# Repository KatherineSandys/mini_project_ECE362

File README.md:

# ECE362_Mini_Project

# Submission 2:

## Internal Peripherals: ADC DAC GPIO SPI I2C

## External Peripherals: Analog SPI I2C

## What are you making?

### Splitting project description into describing the physical hardware, and then what it will be doing.

### Hardware Description:
ILI9341 driven 320x240 3.5" TFT Display controller via SPI.
I2C button matrix (Adafruit Product ID 1616, Trellis 4x4 Keypad) with internal LEDs. LEDs are controlled independently of whether buttons are pushed or not. Button state can be read via I2C, and LED state written via I2C.
Touchscreen on top of TFT: Resistive touchscreen overlay, read via 2 ADC channels giving XY coordinates of touch. calibrated via mapping recorded touch points to position user was told to press on the LCD screen (this is the standard way to calibrate these). Some GPIO used to control additional control signals such as D/C line.
(Tentative, will use if time allows for game menu, otherwise will use button matrix)
-Note- both display and keypad matrix are already owned by a team member and don't need to be purchased.
Audio output: Simple audio output via circuitry used in class to headphones. Will use DAC along with DMA to output music during gameplay.

### Operational Description:
A memory game using buttons. The screen will show you the buttons that need to be pressed along with the corresponding buttons lighting up. 
The screen will show what order each needs to be pressed in by superimposing a number on the representation of the buttons on the screen. 
The screen will only show these details for a short period of time, during which the player must memorize this sequence to be able to win. 
Once the screen stops showing the order and the buttons, the user must then press the buttons in the correct order. 
They have an unlimited amount of time to do so. The more buttons pressed and more sequences that they have been through, the higher the score will be.
Once the display has stopped showing what buttons should be pressed, it will display points, a count-up timer, and a representation of what buttons are currently neing pressed.
Of course, Tetris music will be played during operation for the nice ambiance it has.

## How will you demonstrate it?
The game will be played with music in the background.
The aim is to score as many points possible as you complete the game.
As you press the buttons in the correct order for a given problem the score will increase.
If you do not press the correct buttons in the correct order you do not achieve any remaining points for that level.

## What are the criteria for a successful project?

### Hardware requirements:
full control over contents of display
touchscreen properly calibrated, touch points properly map to intended location of press on the LCD.
no visible delay between pressing of keypad and any requisite lighting of keys.
audible audio, with no unpleasant crackles or pops caused by software delay.

### Software
Points are only awarded for correct gameplay, i.e. only when buttons are pressed in the sequence directed.
Display properly shows the buttons to be pressed as well as the sequence in which they should be pressed.
LEDs on keyad light when sequence is shown.

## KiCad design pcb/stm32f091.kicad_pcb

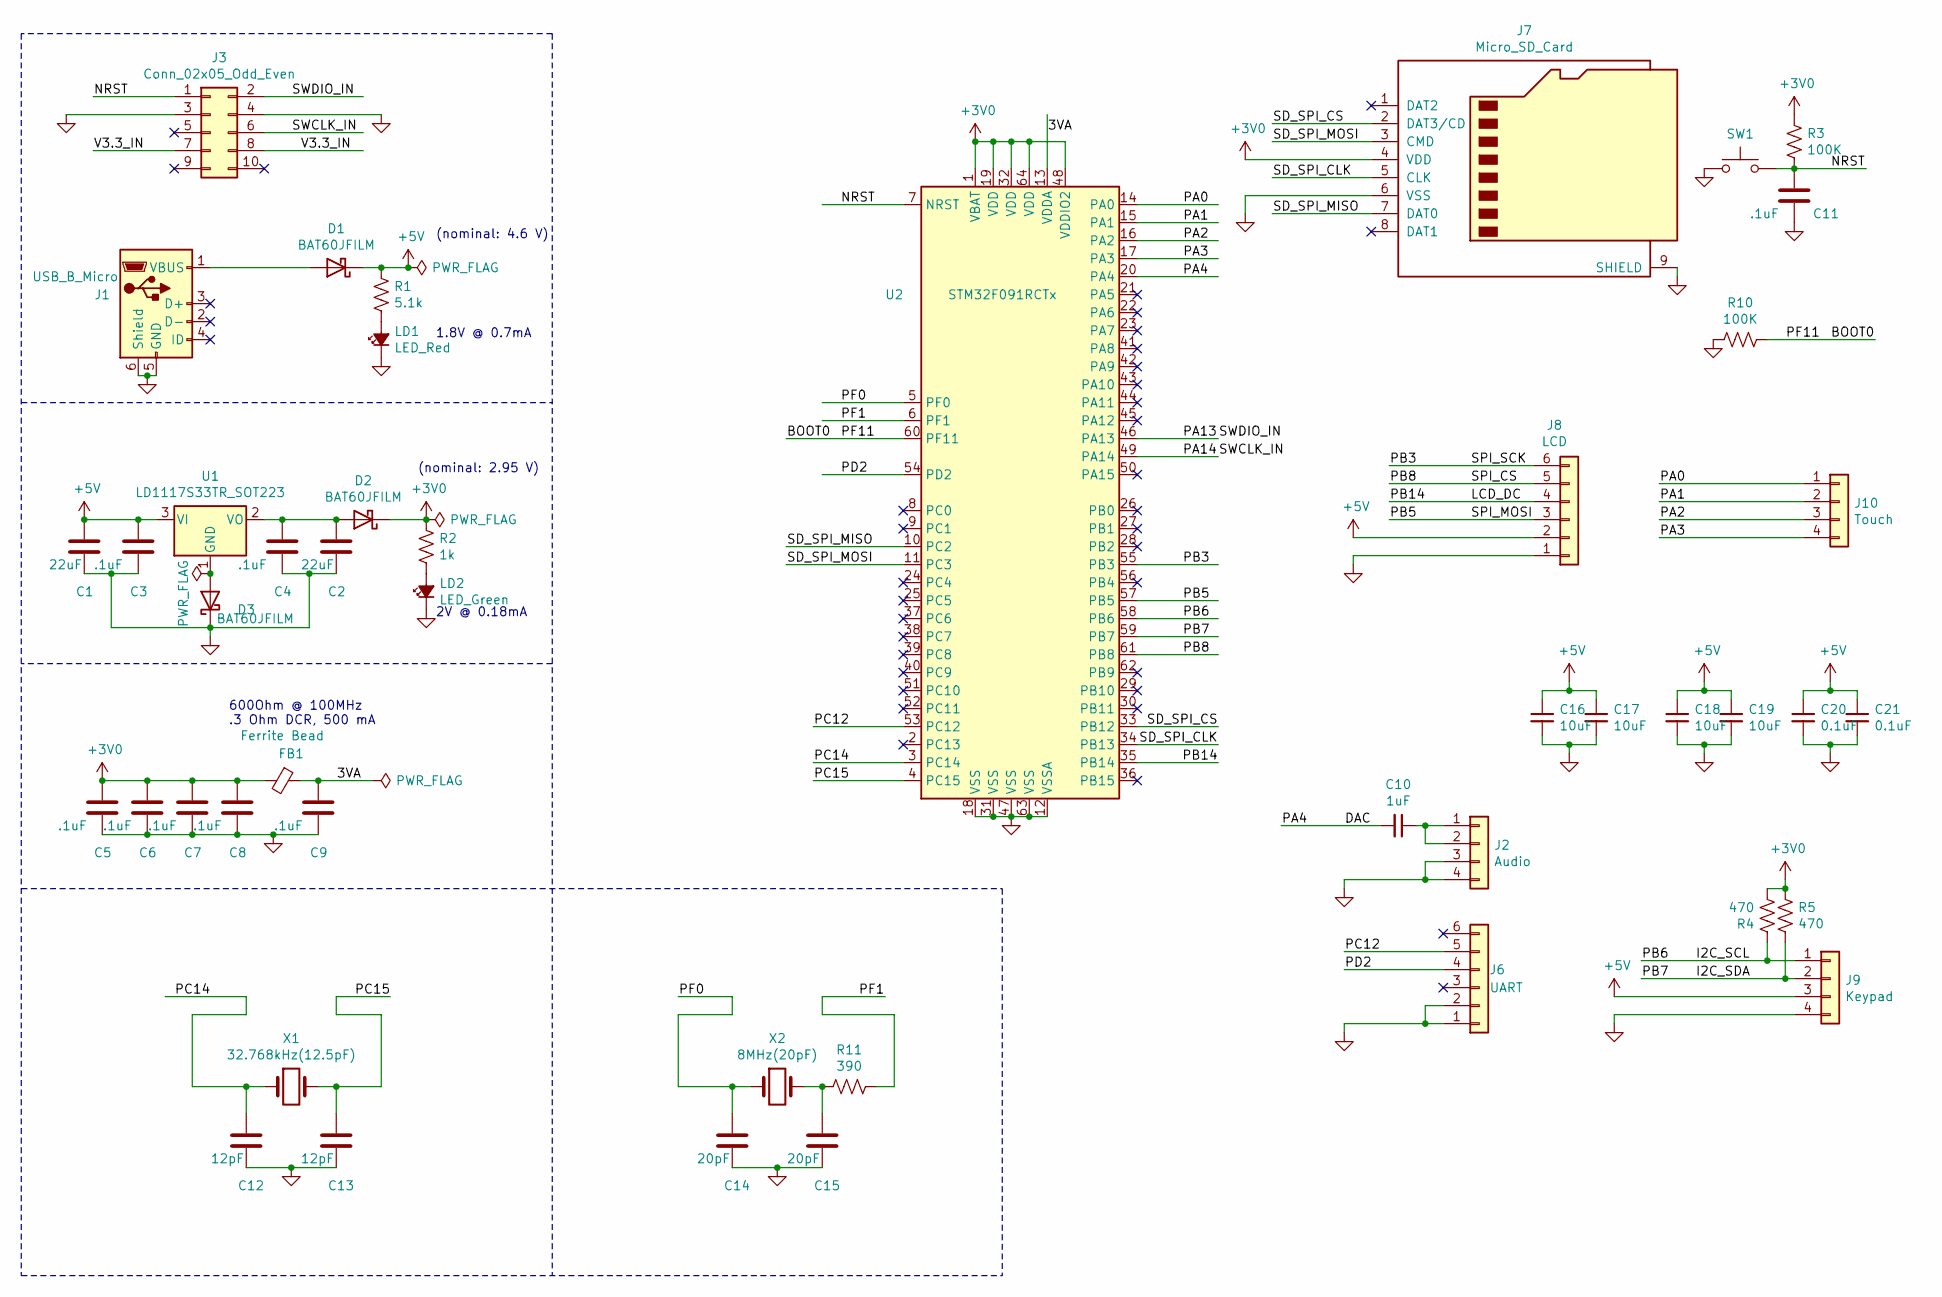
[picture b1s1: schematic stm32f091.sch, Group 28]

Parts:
C1, C2: 22uF; C_0805_2012Metric_Pad1.15x1.40mm_HandSolder
C3, C4, C5, C6, C7, C8, C9, C11: .1uF; C_0805_2012Metric_Pad1.15x1.40mm_HandSolder
C10: 1uF; C_0805_2012Metric_Pad1.15x1.40mm_HandSolder
C12, C13: 12pF; C_0805_2012Metric_Pad1.15x1.40mm_HandSolder
C14, C15: 20pF; C_0805_2012Metric_Pad1.15x1.40mm_HandSolder
C16, C17, C18, C19: 10uF; C_0805_2012Metric_Pad1.15x1.40mm_HandSolder
C20, C21: 0.1uF; C_0805_2012Metric_Pad1.15x1.40mm_HandSolder
D1, D2, D3: BAT60JFILM; D_SOD-323
FB1: Ferrite Bead; L_0805_2012Metric_Pad1.15x1.40mm_HandSolder
J1: USB_B_Micro; USB_Micro-B_Molex_47346-0001
J2: Audio; PinSocket_1x04_P2.54mm_Vertical
J3: Conn_02x05_Odd_Even; IDC-Header_2x05_P2.54mm_Vertical
J6: UART; PinHeader_1x06_P2.54mm_Vertical
J7: Micro_SD_Card; microSD_HC_Wuerth_693072010801
J8: LCD; PinHeader_1x06_P2.54mm_Vertical
J9: Keypad; PinHeader_1x04_P2.54mm_Vertical
J10: Touch; PinHeader_1x04_P2.54mm_Vertical
LD1: LED_Red; LED_0805_2012Metric
LD2: LED_Green; LED_0805_2012Metric
R1: 5.1k; R_0805_2012Metric_Pad1.15x1.40mm_HandSolder
R2: 1k; R_0805_2012Metric_Pad1.15x1.40mm_HandSolder
R3, R10: 100K; R_0805_2012Metric_Pad1.15x1.40mm_HandSolder
R4, R5: 470; R_0805_2012Metric_Pad1.15x1.40mm_HandSolder
R11: 390; R_0805_2012Metric_Pad1.15x1.40mm_HandSolder; LCSC C17477
SW1: SW_Push; SW_SPST_PTS645
U1: LD1117S33TR_SOT223; SOT-223-3_TabPin2
U2: STM32F091RCTx; LQFP-64_10x10mm_P0.5mm
X1: 32.768kHz(12.5pF); ECX-.327-CDX-1293
X2: 8MHz(20pF); Crystal_SMD_3225-4Pin_3.2x2.5mm

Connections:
+3V0: C5.1, C6.1, C7.1, C8.1, D2.1 (K), FB1.2, J7.4 (VDD), R2.1, R3.1, R4.2, R5.1, U2.1 (VBAT), U2.19 (VDD), U2.32 (VDD), U2.48 (VDDIO2), U2.64 (VDD); also elsewhere on the board
+5V: C1.1, C3.1, C16.1, C17.1, C18.1, C19.1, C20.1, C21.1, D1.1 (K), D1.2 (A), J1.1 (VBUS), J8.2, J9.3, R1.1, U1.3 (VI)
/3VA: C9.1, FB1.1, U2.13 (VDDA)
/BOOT0: R10.1, U2.60 (PF11)
/DAC: C10.2, U2.20 (PA4)
/I2C_SCL: J9.1, R4.1, U2.58 (PB6)
/I2C_SDA: J9.2, R5.2, U2.59 (PB7)
/LCD_DC: J8.4, U2.35 (PB14)
/NRST: C11.1, J3.1, R3.2, SW1.2, U2.7 (NRST)
/PA0: J10.1, U2.14 (PA0)
/PA1: J10.2, U2.15 (PA1)
/PA2: J10.3, U2.16 (PA2)
/PA3: J10.4, U2.17 (PA3)
/PA13: J3.2, U2.46 (PA13)
/PA14: J3.6, U2.49 (PA14)
/PB3: J8.6, U2.55 (PB3)
/PB5: J8.3, U2.57 (PB5)
/PB8: J8.5, U2.61 (PB8)
/PC12: J6.5, U2.53 (PC12)
/PC14: C12.1, U2.3 (PC14), X1.1
/PC15: C13.1, U2.4 (PC15), X1.2
/PD2: J6.4, U2.54 (PD2)
/PF0: C14.1, U2.5 (PF0), X2.1
/PF1: R11.1, U2.6 (PF1)
/SD_SPI_CLK: J7.5 (CLK), U2.34 (PB13)
/SD_SPI_CS: J7.2 (DAT3/CD), U2.33 (PB12)
/SD_SPI_MISO: J7.7 (DAT0), U2.10 (PC2); also elsewhere on the board
/SD_SPI_MOSI: J7.3 (CMD), U2.11 (PC3)
/V3.3_IN: J3.7, J3.8
GND: C1.2, C2.2, C3.2, C4.2, C5.2, C6.2, C7.2, C8.2, C9.2, C11.2, C12.2, C13.2, C14.2, C15.2, C16.2, C17.2, C18.2, C19.2, C20.2, C21.2, D3.1 (K), J1.5 (GND), J1.6 (Shield), J2.3, J2.4, J3.3, J3.4, J6.1, J6.2, J7.6 (VSS), J7.9 (SHIELD), J8.1, J9.4, LD1.1 (K), LD2.1 (K), R10.2, SW1.1, U2.12 (VSSA), U2.18 (VSS), U2.31 (VSS), U2.47 (VSS), U2.63 (VSS)
unnamed: C2.1, C4.1, D2.2 (A), U1.2 (VO)
unnamed: C10.1, J2.1, J2.2
unnamed: C15.1, R11.2, X2.2
unnamed: D3.2 (A), U1.1 (GND)
unnamed: LD1.2 (A), R1.2
unnamed: LD2.2 (A), R2.2

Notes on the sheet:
1.8V @ 0.7mA
2V @ 0.18mA
600Ohm @ 100MHz .3 Ohm DCR, 500 mA
(nominal: 4.6 V)
(nominal: 2.95 V)

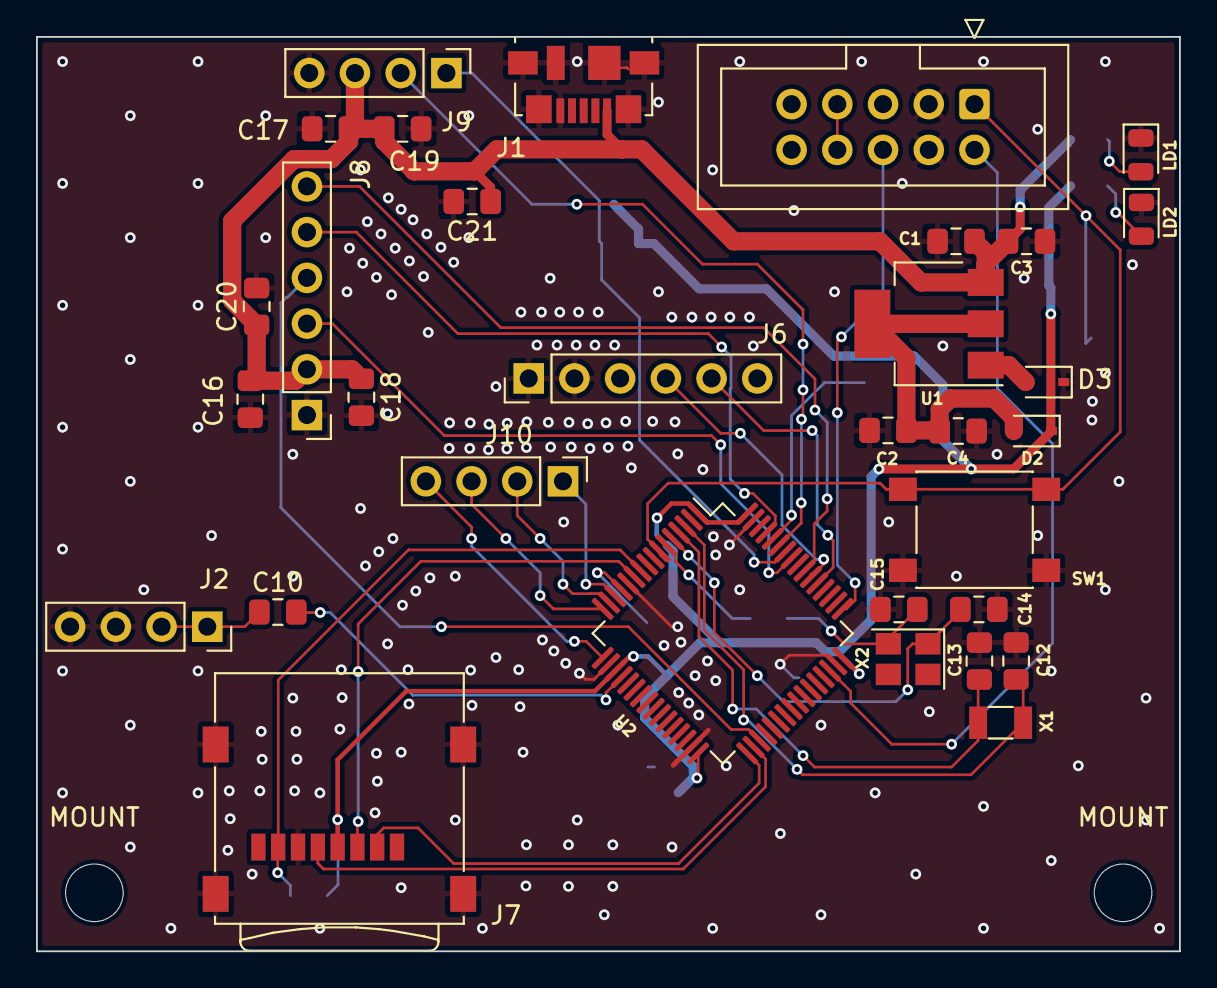
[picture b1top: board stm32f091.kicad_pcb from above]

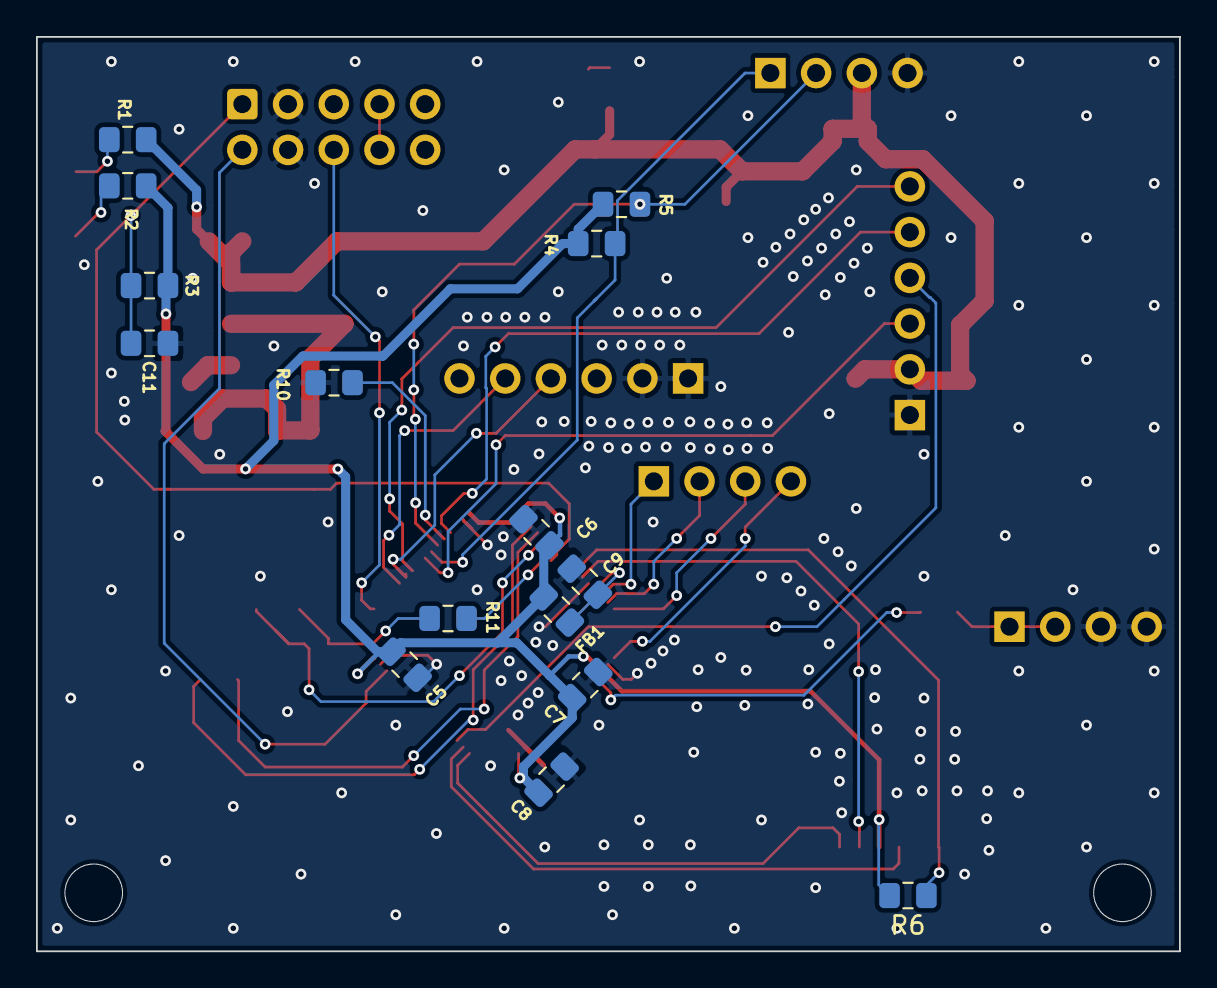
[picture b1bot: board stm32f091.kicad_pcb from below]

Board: 2 copper layers, 63.5 x 50.8 mm, 49 parts (15 on the bottom side), 36 nets.

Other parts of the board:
MOUNT: MountingHole_3.2mm_M3
MOUNT#2: MountingHole_3.2mm_M3
R6: 10K; R_0805_2012Metric_Pad1.15x1.40mm_HandSolder

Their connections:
+3V0: R6.2; also elsewhere on the board
/SD_SPI_MISO: R6.1; also elsewhere on the board

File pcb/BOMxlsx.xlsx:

Id | Designator | Package | Quantity | Designation | Supplier and ref | Column1 | _1
1 | MOUNT,MOUNT | MountingHole_3.2mm_M3 | 2 | MountingHole_3.2mm_M3
2 | J7 | microSD_HC_Wuerth_693072010801 | 1 | Micro_SD_Card
3 | J2 | PinSocket_1x04_P2.54mm_Vertical | 1 | Audio
4 | C10 | C_0805_2012Metric_Pad1.15x1.40mm_HandSolder | 1 | 1uF
5 | U2 | LQFP-64_10x10mm_P0.5mm | 1 | STM32F091RCTx
6 | J3 | IDC-Header_2x05_P2.54mm_Vertical | 1 | Conn_02x05_Odd_Even
7 | U1 | SOT-223-3_TabPin2 | 1 | LD1117S33TR_SOT223
8 | R5,R4 | R_0805_2012Metric_Pad1.15x1.40mm_HandSolder | 2 | 470
9 | C20,C21 | C_0805_2012Metric_Pad1.15x1.40mm_HandSolder | 2 | 0.1uF
10 | C1,C2 | C_0805_2012Metric_Pad1.15x1.40mm_HandSolder | 2 | 22uF
11 | J9 | PinHeader_1x04_P2.54mm_Vertical | 1 | Keypad
12 | X1 | ECX-.327-CDX-1293 | 1 | 32.768kHz(12.5pF)
13 | SW1 | SW_SPST_PTS645 | 1 | SW_Push
14 | X2 | Crystal_SMD_3225-4Pin_3.2x2.5mm | 1 | 8MHz(20pF)
15 | R10,R3 | R_0805_2012Metric_Pad1.15x1.40mm_HandSolder | 2 | 100K
16 | R2 | R_0805_2012Metric_Pad1.15x1.40mm_HandSolder | 1 | 1k
17 | R1 | R_0805_2012Metric_Pad1.15x1.40mm_HandSolder | 1 | 5.1k
18 | FB1 | L_0805_2012Metric_Pad1.15x1.40mm_HandSolder | 1 | Ferrite Bead
19 | C12,C13 | C_0805_2012Metric_Pad1.15x1.40mm_HandSolder | 2 | 12pF
20 | R11 | R_0805_2012Metric_Pad1.15x1.40mm_HandSolder | 1 | 390
21 | C14,C15 | C_0805_2012Metric_Pad1.15x1.40mm_HandSolder | 2 | 20pF
22 | C9,C5,C4,C7,C6,C3,C11,C8 | C_0805_2012Metric_Pad1.15x1.40mm_HandSolder | 8 | .1uF
23 | LD1 | LED_0805_2012Metric | 1 | LED_Red
24 | LD2 | LED_0805_2012Metric | 1 | LED_Green
25 | D2,D3 | D_SOD-323 | 2 | BAT60JFILM
26 | C16,C17,C18,C19 | C_0805_2012Metric_Pad1.15x1.40mm_HandSolder | 4 | 10uF
27 | J1 | USB_Micro-B_Molex_47346-0001 | 1 | USB_B_Micro
28 | J6 | PinHeader_1x06_P2.54mm_Vertical | 1 | UART
29 | J8 | PinHeader_1x06_P2.54mm_Vertical | 1 | LCD
30 | J10 | PinHeader_1x04_P2.54mm_Vertical | 1 | Touch
31 | R6 | R_0805_2012Metric_Pad1.15x1.40mm_HandSolder | 1 | 10K

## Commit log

2021-11-14 mini project starter
2021-11-30 added pcb, some new source files
2021-11-30 added link
2021-11-30 Board dimensions
2021-11-30 initial game logic
2021-11-30 moved keypad into driver file
2021-11-30 update gitignore
2021-11-30 fix main.c
2021-11-30 schematic work
2021-11-30 working on read command
2021-11-30 changes after Tuesday
2021-12-01 schematic complete
2021-12-02 added docs and sch pdf
2021-12-02 keypad drivers complete
2021-12-02 updated keypad header
2021-12-02 added image files
2021-12-02 fixed name conflict
2021-12-02 function name changed
2021-12-02 fun graphic artifact
2021-12-02 added sd card code adapted for SPI2
2021-12-02 Board Layout
2021-12-02 completed pcb
2021-12-02 stitched vias
2021-12-02 moved vias from under pads, fixed trace widths
2021-12-02 added SD_SPI_MISO 10K pullup
2021-12-02 rebased to get keupad.c
2021-12-03 workingish game and countdown timer
2021-12-03 added BOM
2021-12-04 finished first rev of working game logic with LCD and buttons
2021-12-04 added wait to headers
2021-12-04 initial sd card function and tetris file
2021-12-04 change to pb12
2021-12-04 try to add debug config to gitignore
2021-12-04 actually ignore that file
2021-12-04 ignore all .cfg
2021-12-04 more ui and fix same button in row not flashing
2021-12-04 lighting grid for displaying of sequence
2021-12-04 initial audio code
2021-12-06 completed touch code
2021-12-06 polished up headers etc.
2021-12-06 added graphic font
2021-12-06 updated font gaphics functions
2021-12-06 prepped for a splash screen
2021-12-06 fixed timer delay
2021-12-07 initial try again button
2021-12-07 repeating audio working
2021-12-07 moved counter reset
2021-12-07 fixed click on wraparound
2021-12-09 complete audio, fixed touch
2021-12-09 working easy and hard toggle
2021-12-10 recalibrated touch
2021-12-10 should empty queue
